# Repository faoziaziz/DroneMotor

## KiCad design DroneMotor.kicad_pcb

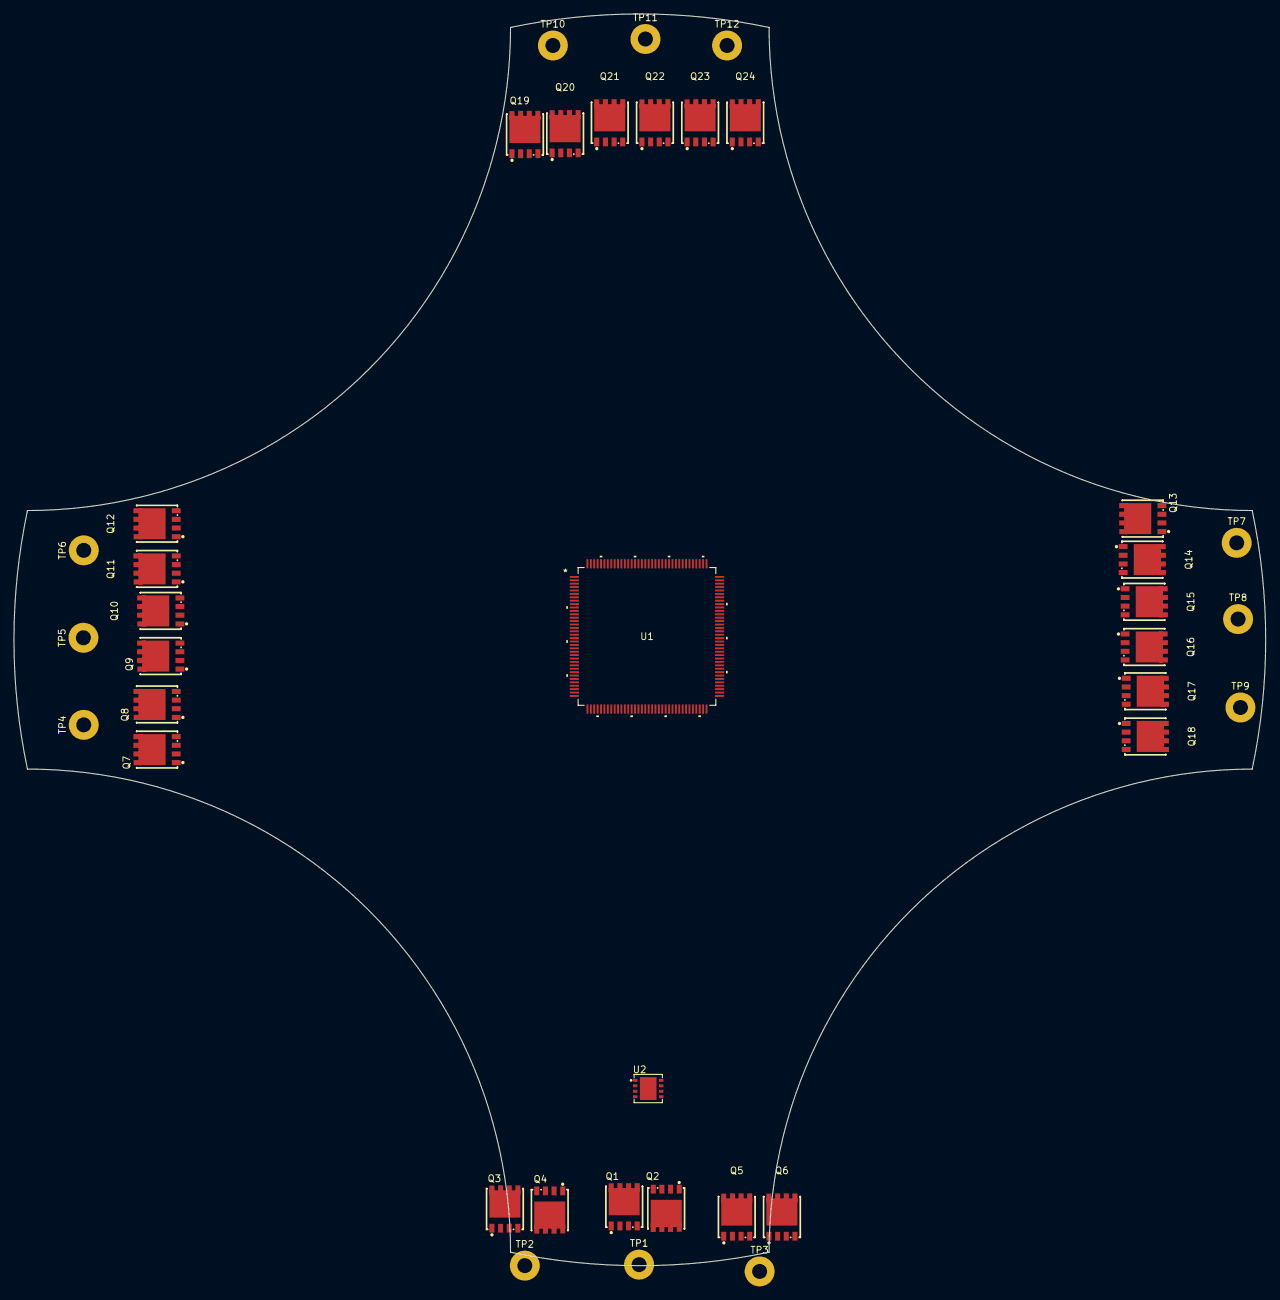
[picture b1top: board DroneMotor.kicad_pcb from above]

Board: 2 copper layers, 184.0 x 184.0 mm, 38 parts (0 on the bottom side), 26 nets, no tracks yet.

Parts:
Q1, Q2, Q3, Q4, Q5, Q6, Q7, Q8, Q9, Q10, Q11, Q12, Q13, Q14, Q15, Q16, Q17, Q18, Q19, Q20, Q21, Q22, Q23, Q24: ISCH54N04NM7V; PG-TDSON-8_L5.0-W6.0-P1.27-BL-EP
TP1, TP2, TP3, TP4, TP5, TP6, TP7, TP8, TP9, TP10, TP11, TP12: HSA; MountingHole_2.2mm_M2_Pad
U1: MKV58F1M0VLQ22; LQFP144_SOT486-2_NXP
U2: UCC27211DRMR; VSON-8_L4.0-W4.0-P0.80-TL-EP

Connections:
+3.3V: U1.5 (VDD1), U1.16 (VDD2), U1.43 (VDD3), U1.56 (VDD4), U1.70 (VDD5), U1.94 (VDD6), U1.108 (VDD7), U1.122 (VDD8), U1.135 (VDD9)
+3.3VA: U1.31 (VDDA), U1.32 (VREFH)
/Controller/M1_INPUT: U1.99 (PTB20), U1.115 (FB_AD5)
/Controller/M1_PWM_A_HS: U1.117 (~UART4_RTS), U1.127 (FLEXPWMB_A0)
/Controller/M2_INPUT: U1.100 (PTB21), U1.116 (~FB_RW)
/Controller/M3_INPUT: U1.101 (PTB22), U1.133 (FB_AD0)
/Controller/M4_INPUT: U1.102 (PTB23), U1.136 (SPI1_SIN)
GNDD: U1.6 (VSS1), U1.17 (VSS2), U1.22 (VSS3), U1.33 (VREFL), U1.34 (VSSA), U1.44 (VSS4), U1.57 (VSS5), U1.71 (VSS6), U1.93 (VSS7), U1.107 (VSS8), U1.121 (VSS9), U1.134 (VSS10)
GNDREF: U2.7 (VSS), U2.9 (PAD)
unnamed: Q2.1 (S), Q2.2 (S), Q2.3 (S), Q4.1 (S), Q4.2 (S), Q4.3 (S), Q6.1 (S), Q6.2 (S), Q6.3 (S)
unnamed: Q8.1 (S), Q8.2 (S), Q8.3 (S), Q10.1 (S), Q10.2 (S), Q10.3 (S), Q12.1 (S), Q12.2 (S), Q12.3 (S)
unnamed: Q14.1 (S), Q14.2 (S), Q14.3 (S), Q16.1 (S), Q16.2 (S), Q16.3 (S), Q18.1 (S), Q18.2 (S), Q18.3 (S)
unnamed: Q20.1 (S), Q20.2 (S), Q20.3 (S), Q22.1 (S), Q22.2 (S), Q22.3 (S), Q24.1 (S), Q24.2 (S), Q24.3 (S)
unnamed: Q1.1 (S), Q1.2 (S), Q1.3 (S), Q2.5 (D), Q2.6 (D), Q2.7 (D), Q2.8 (D), TP1.1, U2.4 (HS)
unnamed: Q7.1 (S), Q7.2 (S), Q7.3 (S), Q8.5 (D), Q8.6 (D), Q8.7 (D), Q8.8 (D), TP4.1
unnamed: Q9.1 (S), Q9.2 (S), Q9.3 (S), Q10.5 (D), Q10.6 (D), Q10.7 (D), Q10.8 (D), TP5.1
unnamed: Q3.1 (S), Q3.2 (S), Q3.3 (S), Q4.5 (D), Q4.6 (D), Q4.7 (D), Q4.8 (D), TP2.1
unnamed: Q5.1 (S), Q5.2 (S), Q5.3 (S), Q6.5 (D), Q6.6 (D), Q6.7 (D), Q6.8 (D), TP3.1
unnamed: Q13.1 (S), Q13.2 (S), Q13.3 (S), Q14.5 (D), Q14.6 (D), Q14.7 (D), Q14.8 (D), TP7.1
unnamed: Q15.1 (S), Q15.2 (S), Q15.3 (S), Q16.5 (D), Q16.6 (D), Q16.7 (D), Q16.8 (D), TP8.1
unnamed: Q19.1 (S), Q19.2 (S), Q19.3 (S), Q20.5 (D), Q20.6 (D), Q20.7 (D), Q20.8 (D), TP10.1
unnamed: Q21.1 (S), Q21.2 (S), Q21.3 (S), Q22.5 (D), Q22.6 (D), Q22.7 (D), Q22.8 (D), TP11.1
unnamed: Q11.1 (S), Q11.2 (S), Q11.3 (S), Q12.5 (D), Q12.6 (D), Q12.7 (D), Q12.8 (D), TP6.1
unnamed: Q17.1 (S), Q17.2 (S), Q17.3 (S), Q18.5 (D), Q18.6 (D), Q18.7 (D), Q18.8 (D), TP9.1
unnamed: Q23.1 (S), Q23.2 (S), Q23.3 (S), Q24.5 (D), Q24.6 (D), Q24.7 (D), Q24.8 (D), TP12.1
VCC_DC+: Q1.5 (D), Q1.6 (D), Q1.7 (D), Q1.8 (D), Q3.5 (D), Q3.6 (D), Q3.7 (D), Q3.8 (D), Q5.5 (D), Q5.6 (D), Q5.7 (D), Q5.8 (D), Q7.5 (D), Q7.6 (D), Q7.7 (D), Q7.8 (D), Q9.5 (D), Q9.6 (D), Q9.7 (D), Q9.8 (D), Q11.5 (D), Q11.6 (D), Q11.7 (D), Q11.8 (D), Q13.5 (D), Q13.6 (D), Q13.7 (D), Q13.8 (D), Q15.5 (D), Q15.6 (D), Q15.7 (D), Q15.8 (D), Q17.5 (D), Q17.6 (D), Q17.7 (D), Q17.8 (D), Q19.5 (D), Q19.6 (D), Q19.7 (D), Q19.8 (D), Q21.5 (D), Q21.6 (D), Q21.7 (D), Q21.8 (D), Q23.5 (D), Q23.6 (D), Q23.7 (D), Q23.8 (D)

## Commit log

2026-01-01 initialized
2026-01-01 add lib
2026-01-03 add rev
2026-04-01 add ti version
